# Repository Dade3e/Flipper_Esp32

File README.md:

Original Marauder code
https://github.com/justcallmekoko/ESP32Marauder/releases/tag/v0.10.4

Original Deauth code
https://github.com/SpacehuhnTech/esp8266_deauther/releases/tag/2.6.1

Hi,
I use ***Esp-wroom-32***, and to save pcap on flipper zero sd:
- Software:
  - Update Arduino ide for recompile marauder esp32 firmware: Arduino Ide Version: 2.1.0;
  - And I configure it with this guide: https://github.com/justcallmekoko/ESP32Marauder/wiki/arduino-ide-setup ;
  - In the marauder project (version 0.10.3), in ***config.h***, uncomment ```#define WRITE_PACKETS_SERIAL```;
  - ***uncomment*** ```#define GENERIC_ESP32``` and comment the others;
  - ADD in ```//// SD DEFINITIONS```:
    ```
    #ifdef GENERIC_ESP32
      #define SD_CS 5
    #endif
    ```
  - in ***esp32_marauder.ino***, modify Serial1 with the serial you want to use: ex. Serial2 in my case: 
    ```
    #ifdef WRITE_PACKETS_SERIAL
        // Starts a second serial channel to stream the captured packets
        Serial2.begin(115200);
      #endif
    ```
  - In ***Buffer.cpp*** modify all Serial1.write in ***void Buffer::forceSaveSerial()*** function  with your Serial: Serial2

 - Hardware: I connect: 
     - Esp32 RX0 => pin13/TX Flipper zero, 
     - ESP32 TX0 0> pin14/RX, 
     - RX2 => pin15/C1, 
     - TX2 => pin16/C0,
     - Vin ESP32 pin to 5V Flipper zero pin, to be enabled in the main GPIO section,
     - GND Esp32 pin to GND Flipper zero pin

I think this is all :/

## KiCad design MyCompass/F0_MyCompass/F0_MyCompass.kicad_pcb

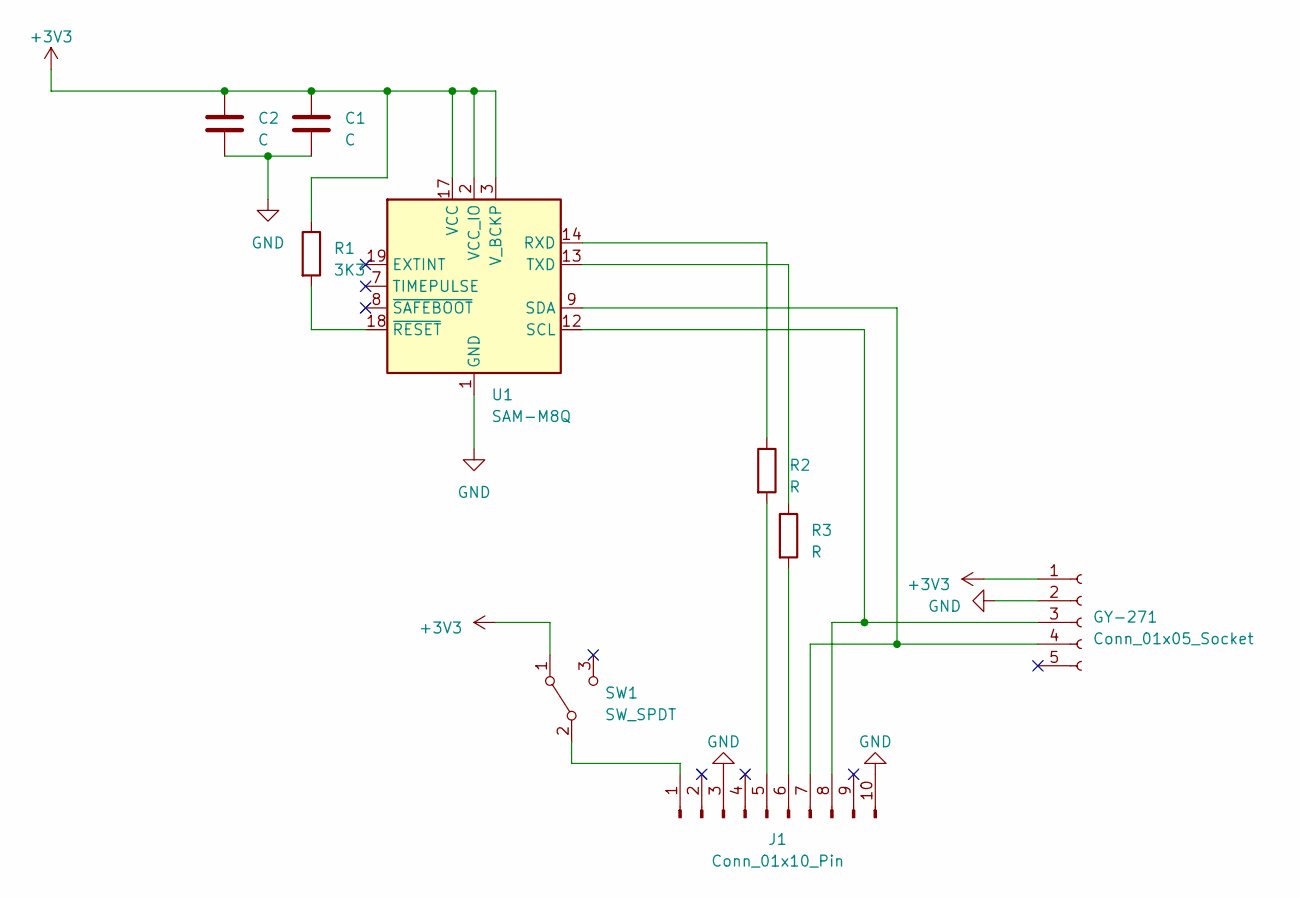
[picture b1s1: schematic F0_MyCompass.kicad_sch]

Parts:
C1, C2: C; C_0805_2012Metric_Pad1.18x1.45mm_HandSolder
GY-271: Conn_01x05_Socket; GY-271
J1: Conn_01x10_Pin; PinHeader_1x10_P2.54mm_Vertical
R1: 3K3; R_0603_1608Metric_Pad0.98x0.95mm_HandSolder
R2, R3: R; R_0603_1608Metric_Pad0.98x0.95mm_HandSolder
SW1: SW_SPDT; SW_SPDT_PCM12
U1: SAM-M8Q; ublox_SAM-M8Q

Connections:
+3V3: C1.1, C2.1, GY-271.1, R1.1, SW1.1 (A), U1.2 (VCC_IO), U1.3 (V_BCKP), U1.17 (VCC)
GND: C1.2, C2.2, GY-271.2, J1.3, J1.10, U1.1 (GND), U1.4 (GND), U1.5 (GND), U1.6 (GND), U1.10 (GND), U1.11 (GND), U1.15 (GND), U1.16 (GND), U1.20 (GND)
unnamed: GY-271.3, J1.8, U1.12 (SCL)
unnamed: GY-271.4, J1.7, U1.9 (SDA)
unnamed: J1.1, SW1.2 (B)
unnamed: J1.5, R2.2
unnamed: J1.6, R3.2
unnamed: R2.1, U1.14 (RXD)
unnamed: R3.1, U1.13 (TXD)
unnamed: R1.2, U1.18 (~RESET)

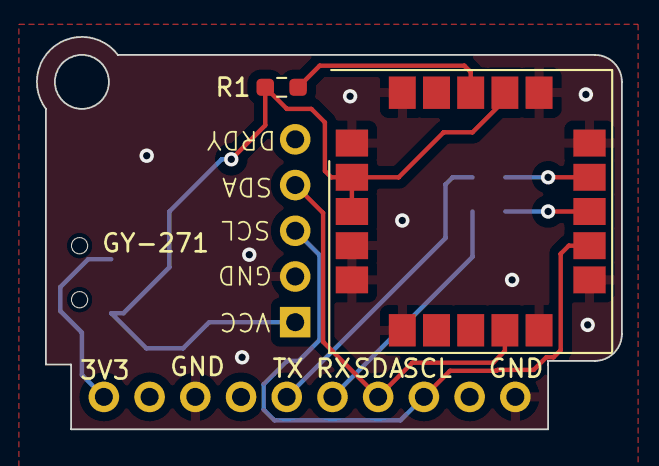
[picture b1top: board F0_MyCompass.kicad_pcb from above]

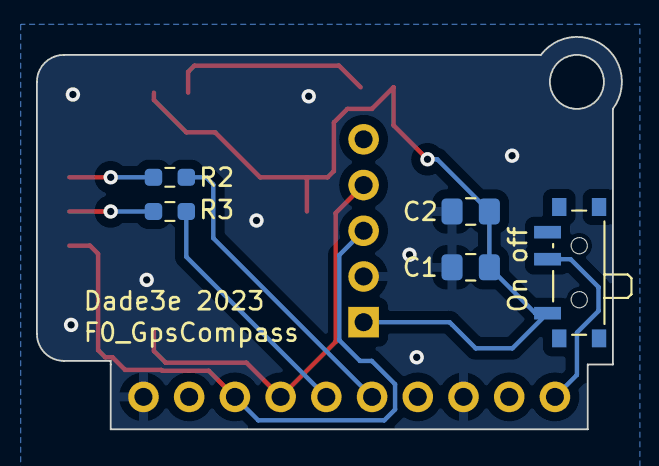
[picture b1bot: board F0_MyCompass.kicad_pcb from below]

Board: 2 copper layers, 32.5 x 21.8 mm, 9 parts (5 on the bottom side), 10 nets.

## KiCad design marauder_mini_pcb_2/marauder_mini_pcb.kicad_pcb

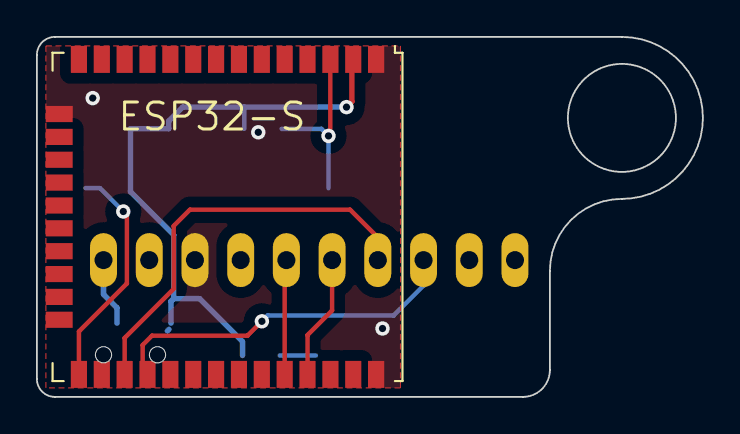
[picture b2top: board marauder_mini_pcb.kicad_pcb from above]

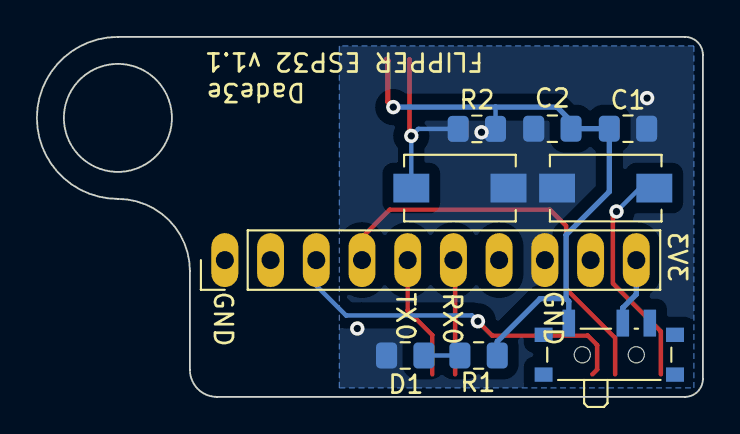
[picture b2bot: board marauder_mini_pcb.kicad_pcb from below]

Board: 2 copper layers, 37.0 x 20.0 mm, 10 parts (9 on the bottom side), 10 nets.

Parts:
C1, C2: C; C_0805_2012Metric_Pad1.18x1.45mm_HandSolder
D1: LED; C_0805_2012Metric_Pad1.18x1.45mm_HandSolder
J1: Conn_01x10; PinHeader_1x10_P2.54mm_Vertical_largo
R1: R; C_0805_2012Metric_Pad1.18x1.45mm_HandSolder
R2: 10K; C_0805_2012Metric_Pad1.18x1.45mm_HandSolder
SW1: SW_SPDT; SW_SPDT_PCM12
SW2, SW3: SW_Push; SW_SPST_EVQPE1
U1: ESP32-WROOM-32; ESP32-WROOM-32U

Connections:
GND: C1.2, C2.2, D1.1 (K), J1.8, SW2.2, SW3.1, U1.1 (GND), U1.15 (GND), U1.38 (GND)
unnamed: D1.2 (A), R1.1
unnamed: J1.3, U1.28 (IO17)
unnamed: J1.4, U1.27 (IO16)
unnamed: J1.5, U1.35 (TXD0/IO1)
unnamed: J1.6, U1.34 (RXD0/IO3)
unnamed: J1.10, SW1.2 (B)
unnamed: C1.1, C2.1, R1.2, R2.1, SW1.1 (A), U1.2 (VDD)
unnamed: R2.2, SW3.2, U1.3 (EN)
unnamed: SW2.1, U1.25 (IO0)

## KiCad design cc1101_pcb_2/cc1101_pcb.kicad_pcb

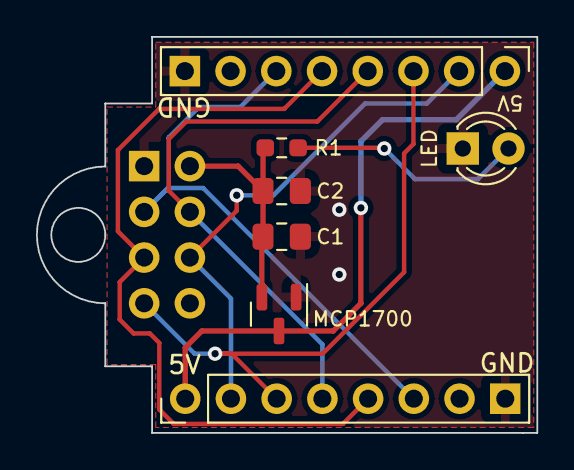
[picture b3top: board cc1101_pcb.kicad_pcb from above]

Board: 2 copper layers, 27.8 x 22.0 mm, 8 parts (1 on the bottom side), 9 nets.

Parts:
C1, C2: C; C_0805_2012Metric_Pad1.18x1.45mm_HandSolder
J1, J2: Conn_01x08_MountingPin; PinHeader_1x08_P2.54mm_Vertical
J3: Conn_02x04_Odd_Even_Shielded; PinSocket_2x04_P2.54mm_Vertical
LED: LED; LED_D3.0mm
MCP1700: MCP1700x-330xxTT; SOT-23
R1: R; R_0603_1608Metric_Pad0.98x0.95mm_HandSolder

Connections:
GND: C1.2, C2.2, J1.8, J2.8, J3.1, LED.1 (K), MCP1700.1 (GND)
unnamed: LED.2 (A), R1.1
unnamed: J1.1, J2.1, MCP1700.3 (VI)
unnamed: J1.2, J2.2, J3.6
unnamed: J1.3, J2.3, J3.7
unnamed: J1.4, J2.4, J3.4
unnamed: J1.5, J2.5, J3.5
unnamed: J1.6, J2.6, J3.3
unnamed: C1.1, C2.1, J3.2, MCP1700.2 (VO), R1.2

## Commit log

2023-05-15 Aggiornato circuito
2023-05-15 Passato alla versione v0.10.4
2023-05-21 Aggiunto ESP8266DEAUTH
2023-05-25 Prova new pcb
2023-05-26 Aggiunta versione migliorata per antenna esterna
2023-05-27 Aggiunta pcb cc1101
2023-05-29 Aggiunta pcb che puoi girare
2023-05-30 Modifiche varie che non voglio controllare
2023-06-06 Aggiornamenti vari
2023-06-10 Aggiunta immagine settings arduino ide e aggiornate pcbs
2023-07-03 Aggiornato marauder e pcb
2023-07-03 Aggiornato marauder a v0.10.8
